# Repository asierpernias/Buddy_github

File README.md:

# Buddy
A small size pocket friend with animated eyes. Buddy runs on a XIAO ESP32-S3 with a 2" LCD and, through a imu (LIS2DH12), reacts to how you handle it.

## Features
- Animated eyes drawn off-screen and pushed in a single transfer to the screen so ther is no flicker.
- Eyes follow the edge of the board.
- Shake / Upside down detection and reaction.
- Side button to cycle thrugh three moods (normal / happy / sleepy)
- Customized PCB with multicolor silkscreen and a hole for a carabiner to attach it as a keychain.

## Firmware

The code is in `code/code.ino`.
 
1. Install the ESP32 board package and select XIAO_ESP32S3
2. Install Adafruit GFX Library and Adafruit ST7789 Library.
3. Upload the sketch.

## BOM
| Designator | Footprint | Qty | Value | LCSC Part # | Total (USD) |
|---|---|---|---|---|---|
| C3, C4 | 0402 | 2 | 100nF | C1525 | 0.002 |
| CN1 | CONN-SMD_P2.00_S2B-PH-SM4-TB-LF-SN | 1 | S2B-PH-SM4-TB | C295747 | 0.22 |
| R1, R2 | 0402 | 2 | 4.7k | C25900 | 0.001 | 0.002 |
| SW1 | KEY-SMD_1TS003B | 1 | 1TS003B-1400-3500A | C319392 | 0.04 |
| U2 | LGA-12_L2.0-W2.0-P0.50-BL | 1 | LIS2DH12TR | C110926 | 0.61 |
| U3 | XIAO-ESP32-S3-SMD | 1 | XIAO ESP32-S3 | n/a (Seeed Studio) | 7.49 |
| WAVESHARE_SCREEN | PinHeader_1x08_P2.54mm_Vertical | 1 | Waveshare 2inch LCD Module | n/a (Waveshare) |  14.28 |
| **PCB** | $8.96 | **PCBA assembly** | $82.6  | Total PCB fabricatipm | $91.54 |
**Total**  **≈ $112** 

## Screenshots

## LICENSE

This project is under the MIT License. Read `LICENSE.md` for more information.

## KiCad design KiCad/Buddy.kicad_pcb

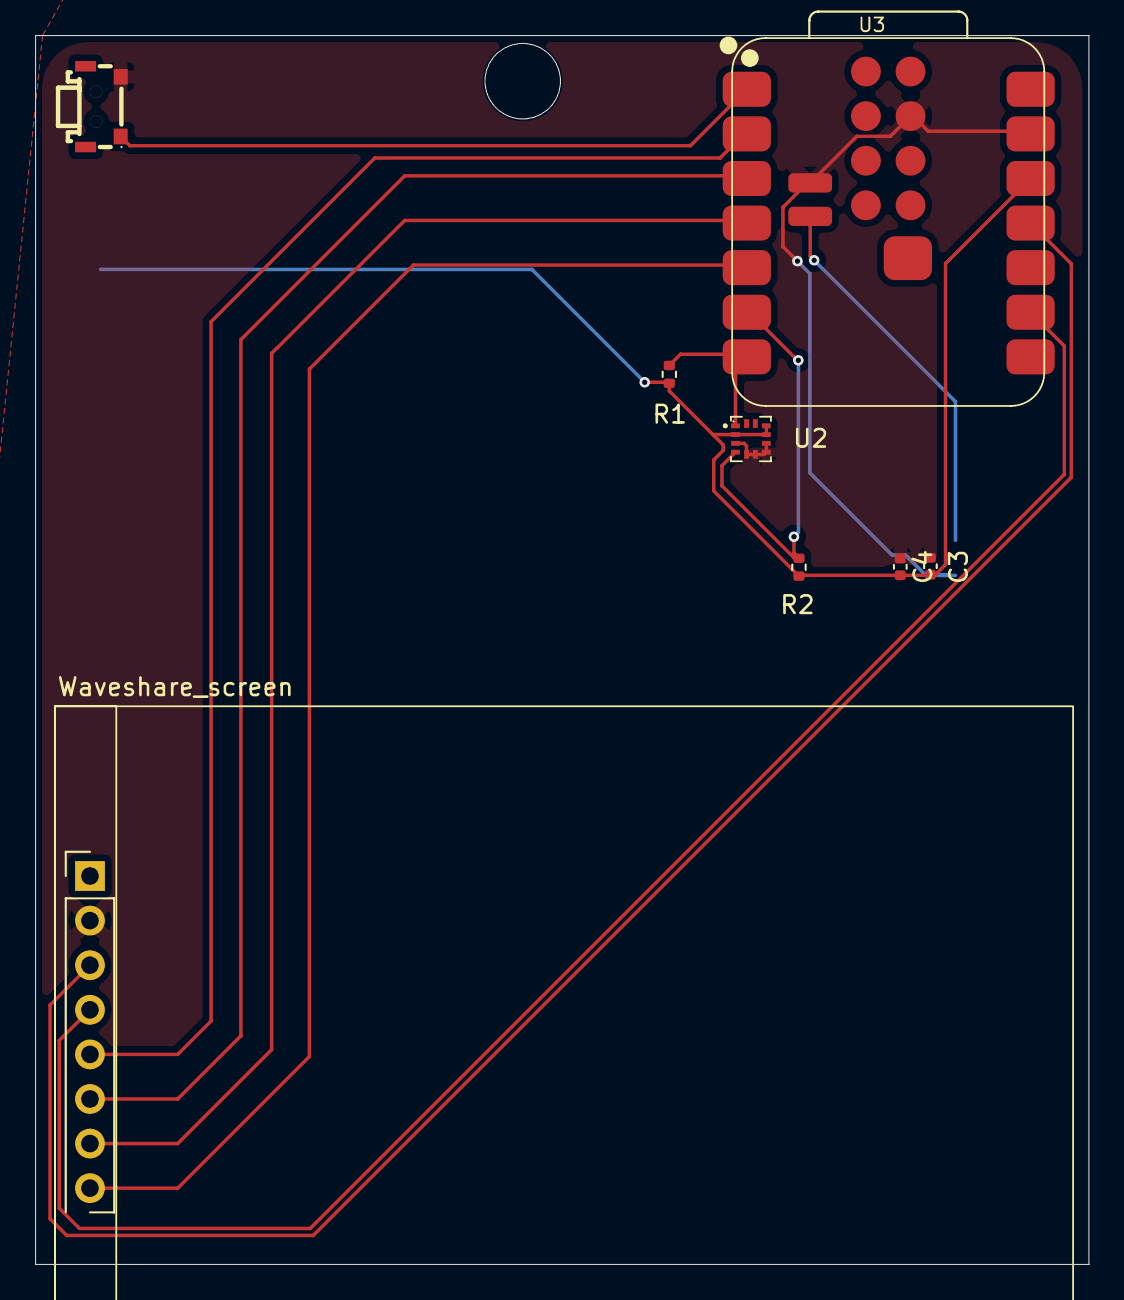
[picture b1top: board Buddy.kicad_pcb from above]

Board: 2 copper layers, 60.0 x 70.0 mm, 9 parts (1 on the bottom side), 12 nets.

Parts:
C3, C4: 100nf; C_0402_1005Metric
CN1: S2B-PH-SM4-TB; CONN-SMD_P2.00_S2B-PH-SM4-TB-LF-SN
R1, R2: 4.7k; R_0402_1005Metric
SW1: 1TS003B-1400-3500A; KEY-SMD_1TS003B
U2: LIS2DH12TR; LGA-12_L2.0-W2.0-P0.50-BL
U3: XIAO-ESP32-S3-SMD
Waveshare_screen: PinHeader_1x08_P2.54mm_Vertical

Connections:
/3V3: C3.2, C4.2, R1.2, R2.2, U2.2 (CS), U2.9 (VDD), U2.10 (VDD_IO), U3.12 (3V3_OUT), Waveshare_screen.1 (VCC)
/D0: SW1.1, U3.1 (D0)
/D1: U3.2 (D1), Waveshare_screen.5 (CS)
/D2: U3.3 (D2), Waveshare_screen.6 (DC)
/D3: U3.4 (D3), Waveshare_screen.7 (RST)
/D4: U3.5 (D4), Waveshare_screen.8 (BL)
/D5-A: R2.1, U2.4 (SDA/SDI/SDO), U3.6 (D5)
/D6-A: R1.1, U2.1 (SCL/SPC), U3.7 (D6)
/D8: U3.9 (D8), Waveshare_screen.4 (CLK)
/D10: U3.11 (D10), Waveshare_screen.3 (DIN)
GND: C3.1, C4.1, CN1.2, SW1.2, U2.3 (SDO/SA0), U2.5 (RES), U2.6 (GND), U2.7 (GND), U2.8 (GND), U3.13 (GND), U3.18 (GND), U3.24 (GND), Waveshare_screen.2 (GND)
unnamed: CN1.1, U3.23 (VBAT)

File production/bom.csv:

Designator,Footprint,Quantity,Value,LCSC Part #
"C3, C4",0402,2,100nf,
CN1,CONN-SMD_P2.00_S2B-PH-SM4-TB-LF-SN,1,S2B-PH-SM4-TB,C295747
"R1, R2",0402,2,4.7k,
SW1,KEY-SMD_1TS003B,1,1TS003B-1400-3500A,C319392
U2,LGA-12_L2.0-W2.0-P0.50-BL,1,LIS2DH12TR,C110926
U3,XIAO-ESP32-S3-SMD,1,XIAO-ESP32-S3-SMD,
WAVESHARE_SCREEN,PinHeader_1x08_P2.54mm_Vertical,1,~,
